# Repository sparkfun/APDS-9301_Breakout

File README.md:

SparkFun APDS-9301 Lux Sensor Breakout
======================================

[*APDS-9301 Lux Sensor Breakout (SEN-14350)*](https://www.sparkfun.com/products/14350)

The APDS-9301 Lux Sensor Breakout is a small I<sup>2</sup>C based sensor with dynamic range. 

Repository Contents
-------------------
* **/Hardware** - All Eagle design files (.brd, .sch)
* **/Libraries** - All Arduino libraries and board examples
* **/Production** - Test bed files and production panel files

Documentation
--------------
* **[Library](https://github.com/sparkfun/SparkFun_APDS9301_Library)** - Arduino library for the APDs-9301.
* **[Hookup Guide](https://learn.sparkfun.com/tutorials/apds-9301-sensor-hookup-guide)** - Basic hookup guide for the APDS-9301 Breakout Board.

License Information
-------------------

This product is _**open source**_! 

Please review the LICENSE.md file for license information. 

If you have any questions or concerns on licensing, please contact techsupport@sparkfun.com.

Distributed as-is; no warranty is given.

- Your friends at SparkFun.

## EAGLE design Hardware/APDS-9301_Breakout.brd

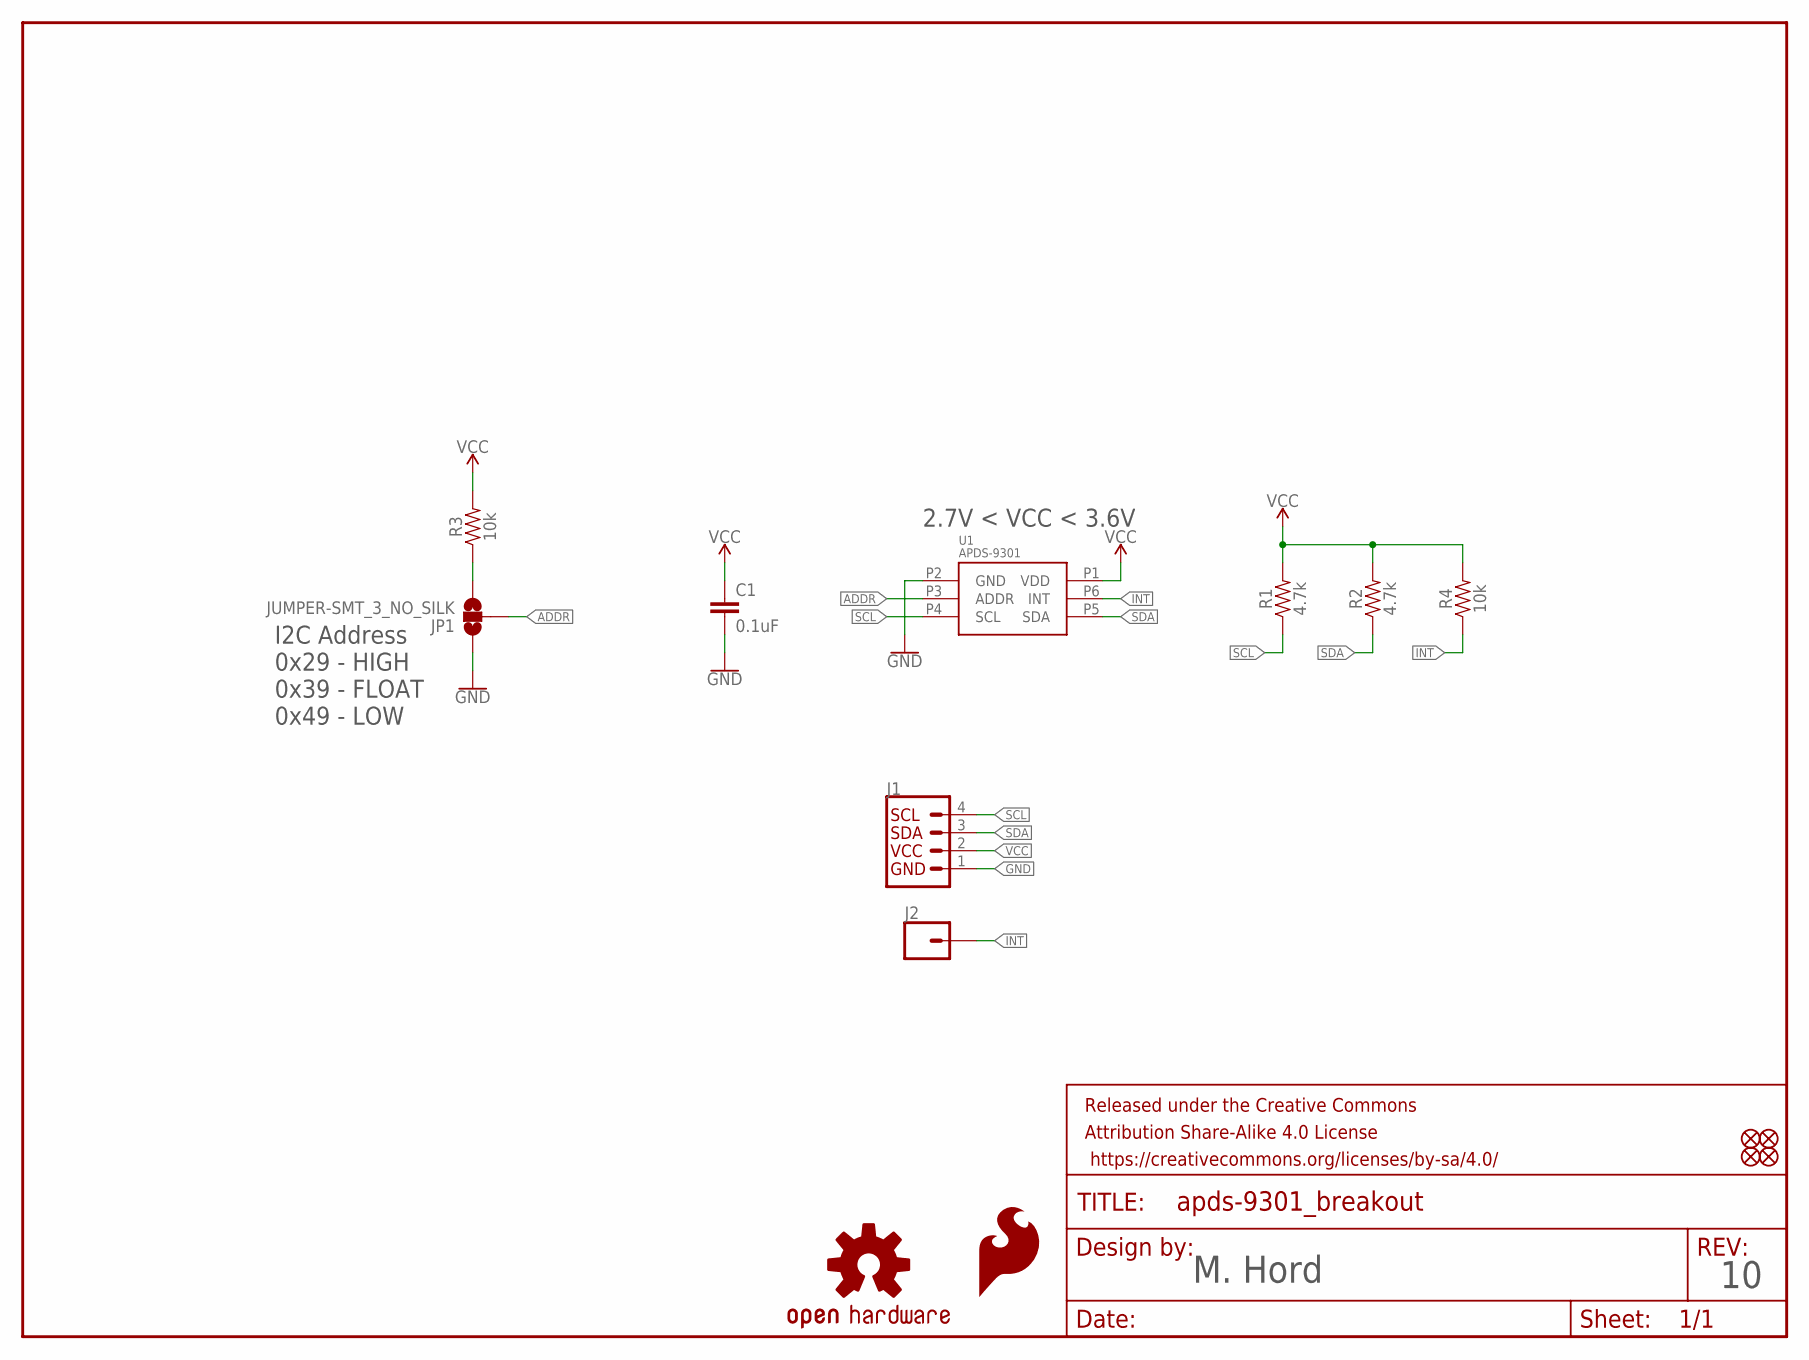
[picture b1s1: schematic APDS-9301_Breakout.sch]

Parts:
C1: 0.1uF; 0603
FD1, FD2, FD3, FD4: FIDUCIALUFIDUCIAL; FIDUCIAL-MICRO
FRAME1: FRAME-LETTER; CREATIVE_COMMONS
J1: I2C_STANDARD; 1X04
J2: CONN_01; 1X01
JP1: JUMPER-SMT_3_NO_SILK; SMT-JUMPER_3_NO_SILK
LOGO1: SFE_LOGO_FLAME.1_INCH; SFE_LOGO_FLAME_.1
LOGO2: OSHW-LOGOS; OSHW-LOGO-S
R1, R2: 4.7k; 0603
R3, R4: 10k; 0603
U1: APDS-9301; CHIPLED-6

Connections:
ADDR: JP1.2, U1.P3 (ADDR)
GND: C1.2, J1.1, JP1.1, U1.P2 (GND)
INT: J2.1, R4.1, U1.P6 (INT)
unnamed: JP1.3, R3.1
SCL: J1.4, R1.1, U1.P4 (SCL)
SDA: J1.3, R2.1, U1.P5 (SDA)
VCC: C1.1, J1.2, R1.2, R2.2, R3.2, R4.2, U1.P1 (VDD)

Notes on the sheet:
I2C Address 0x29 - HIGH 0x39 - FLOAT 0x49 - LOW
M. Hord
2.7V < VCC < 3.6V

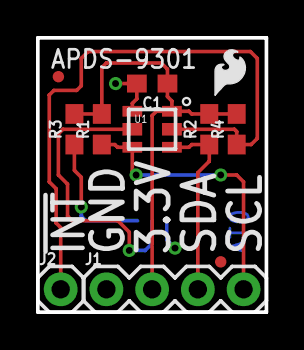
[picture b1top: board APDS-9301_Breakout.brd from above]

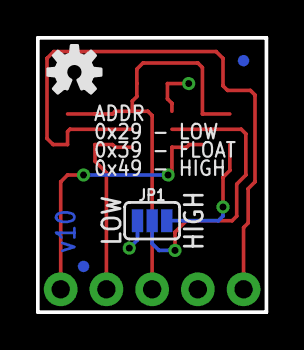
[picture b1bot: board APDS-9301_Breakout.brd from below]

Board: 2 copper layers, 12.7 x 15.2 mm, 16 parts (4 on the bottom side), 7 nets.

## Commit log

2017-06-21 Change to V10, chg silk on back of board
2017-06-21 Changes for V10 post checklist
2017-06-21 Inc size of notes on sch, add units to layout
2017-09-06 Add READMe
2017-09-06 Squashed 'Libraries/Arduino/' content from commit 7595d45
    git-subtree-dir: Libraries/Arduino
    git-subtree-split: 7595d45bbb3fc895e26e9b377189db1309d71061
2018-01-24 Squashed 'Libraries/Arduino/' changes from 7595d45..3ca370c
    3ca370c Fix scaling issue
    git-subtree-dir: Libraries/Arduino
    git-subtree-split: 3ca370cddcbc2f70a95a1afb560b8c82b7a9dcc9

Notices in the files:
parts and their libraries:
SparkFun-Capacitors: Licensing: Creative Commons ShareAlike 4.0 International - https://creativecommons.org/licenses/by-sa/4.0
SparkFun-Aesthetics: Released under the Creative Commons Attribution Share-Alike 4.0 License
SparkFun-Aesthetics: https://creativecommons.org/licenses/by-sa/4.0
